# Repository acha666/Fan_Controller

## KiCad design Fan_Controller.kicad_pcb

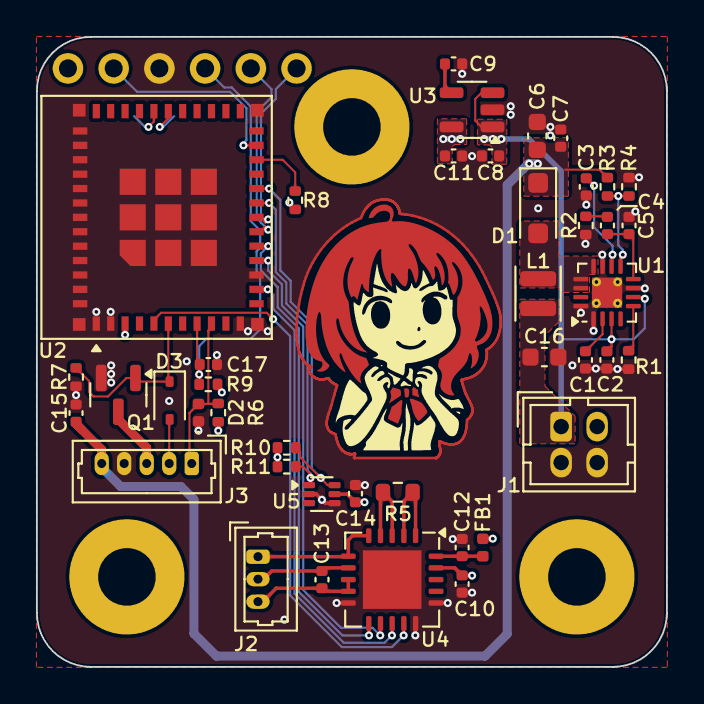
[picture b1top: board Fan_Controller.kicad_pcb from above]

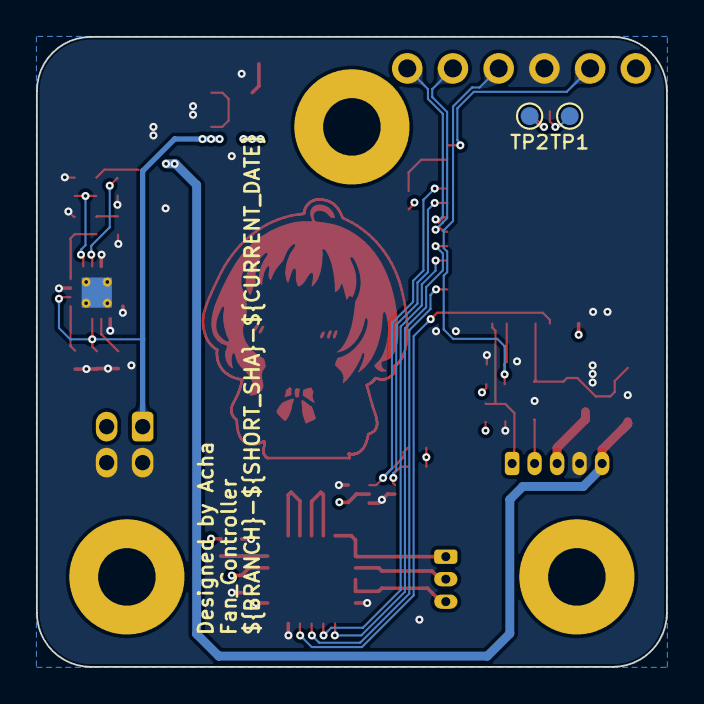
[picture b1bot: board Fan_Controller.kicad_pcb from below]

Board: 4 copper layers, 35.0 x 35.0 mm, 45 parts (2 on the bottom side), 35 nets.

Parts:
C1, C8, C11, C17: 1uF; C_0402_1005Metric
C2, C7, C10, C12, C15: 100nF; C_0402_1005Metric
C3, C14: 10nF; C_0402_1005Metric
C4: 15nF; C_0402_1005Metric
C5: 300pF; C_0402_1005Metric
C6: 10uF; C_0603_1608Metric
C9: 22nF; C_0402_1005Metric
C13: 100nF/10nF; C_0402_1005Metric
C16: 2.2uF; C_0603_1608Metric
D1: MBR1020VL; D_SOD-123F
D2: D_TVS; D_0402_1005Metric
D3: 1N4148WS; D_SOD-323
FB1: 120R@100MHz; L_0402_1005Metric
J1: DF11-4DP-2DSA; Hirose_DF11-4DP-2DSA_2x02_P2.00mm_Vertical
J2: 53047-0310; Molex_PicoBlade_53047-0310_1x03_P1.25mm_Vertical
J3: 53047-0510; Molex_PicoBlade_53047-0510_1x05_P1.25mm_Vertical
J4: TP_01x06_P2.54; PinHeader_1x06_P2.54mm_Vertical
L1: 2.2uH; L_Sunlord_SWPA252012S
Q1: AO3400A; SOT-23
R1: 9.76K; R_0402_1005Metric
R2: 412R; R_0402_1005Metric
R3: 27.4K; R_0402_1005Metric
R4: 2.49K; R_0402_1005Metric
R5: 430R/4.3K; R_0603_1608Metric
R6, R8, R9: 10K; R_0402_1005Metric
R7: 100K; R_0402_1005Metric
R10, R11: 5.1K; R_0402_1005Metric
TP1, TP2: TestPoint; TestPoint_Pad_D1.0mm
U1: LM51571; WQFN-16-1EP_3x3mm_P0.5mm_EP1.68x1.68mm_ThermalVias
U2: ESP32-C6-MINI-1; ESP32-C6-MINI-1U
U3: RT9193-33GB; SOT-23-5
U4: MAX31865xTP; TQFN-20-1EP_5x5mm_P0.65mm_EP3.25x3.25mm
U5: TMP112xxDRL; SOT-563

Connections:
+3V3: C10.1, C11.1, C14.1, FB1.1, J4.1, R6.1, R8.1, R9.1, R10.1, R11.1, U2.3 (3V3), U3.5 (VOUT), U4.19 (DVDD), U5.5 (V+)
+5V: C2.2, C8.1, C16.1, J1.1, L1.1, U1.3 (BIAS), U1.6 (UVLO/SYNC/EN), U3.1 (VIN), U3.3 (EN)
+12V: C6.1, C7.1, C15.1, D1.1 (K), J3.5, R3.1
/D+: J4.6, U2.18 (IO13)
/D-: J4.5, U2.17 (IO12)
/EN: C17.1, J4.4, R9.2, U2.8 (EN)
/IO3: D3.1 (K), Q1.1 (G), R7.1, U2.6 (IO3)
/IO4: D2.2 (A2), J3.1, R6.2, U2.9 (IO4)
/IO8: R8.2, U2.22 (IO8)
/IO9: J4.2, U2.23 (IO9)
/RXD: TP2.1, U2.30 (RXD0)
/SCL: R11.2, U2.19 (IO14), U5.1 (SCL)
/SDA: R10.2, U2.20 (IO15), U5.6 (SDA)
/SPICLK: U2.15 (IO6), U4.12 (SCLK)
/SPICS: U2.13 (IO1), U4.13 (~CS)
/SPIMISO: U2.5 (IO2), U4.14 (SDO)
/SPIMOSI: U2.16 (IO7), U4.11 (SDI)
/TXD: TP1.1, U2.31 (TXD0)
GND: C1.1, C2.1, C3.1, C5.2, C6.2, C7.2, C8.2, C9.2, C10.2, C11.2, C12.2, C14.2, C15.2, C16.2, C17.2, D2.1 (A1), J1.2, J1.4, J3.4, J4.3, Q1.2 (S), R1.1, R2.2, R4.2, R7.2, U1.1 (PGND), U1.7 (AGND), U1.11 (MODE), U1.16 (PGND), U1.17 (EP), U2.1 (GND), U2.2 (GND), U2.11 (GND), U2.14 (GND), U2.36 (GND), U2.37 (GND), U2.38 (GND), U2.39 (GND), U2.40 (GND), U2.41 (GND), U2.42 (GND), U2.43 (GND), U2.44 (GND), U2.45 (GND), U2.46 (GND), U2.47 (GND), U2.48 (GND), U2.49 (GND), U2.50 (GND), U2.51 (GND), U2.52 (GND), U2.53 (GND), U3.2 (GND), U4.10 (GND), U4.15 (DGND), U4.16 (GND), U4.21 (GND), U5.2 (GND), U5.4 (ADD0)
unnamed: C4.2, R2.1
unnamed: D1.2 (A), L1.2, U1.12 (SW), U1.13 (SW), U1.14 (SW)
unnamed: D3.2 (A), J3.2
unnamed: J2.1, U4.5 (FORCE+), U4.6 (FORCE2)
unnamed: C13.1, J2.2, U4.7 (RTDIN+)
unnamed: C13.2, J2.3, U4.8 (RTDIN-), U4.9 (FORCE-)
unnamed: J3.3, Q1.3 (D)
unnamed: C4.1, C5.1, U1.8 (COMP)
unnamed: R3.2, R4.1, U1.9 (FB)
unnamed: R1.2, U1.5 (RT)
unnamed: C3.2, U1.10 (SS)
unnamed: C1.2, U1.2 (VCC)
unnamed: C9.1, U3.4 (BP)
unnamed: R5.1, U4.1 (BIAS), U4.2 (REFIN+)
unnamed: R5.2, U4.3 (REFIN-), U4.4 (ISENSOR)
unnamed: C12.1, FB1.2, U4.20 (VDD)

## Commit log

2025-05-09 CI Update
2025-05-09 Fix upload-artifact version
2025-05-11 Workflow Update
2025-05-11 Workflow bugs fixed
2025-05-11 Fix SCH and BOM release upload
2025-05-30 Gerber Export: --subtract-soldermask
